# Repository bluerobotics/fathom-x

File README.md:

# Fathom-X and Fathom-E

The Fathom-X and -E Tether Boards are part of Blue Robotics' *Fathom Tether* system. These boards provide interfaces and functionality for the communication methods used with the tether. With the Fathom tether, it is quick and easy to get up and running and interface with your ROV or other application.

The schematic and board layout are designed in EagleCAD.

# Fathom-E (Simple Ethernet) Hardware

## Description

The Fathom-E board provides a simple and economical way to connect the Fathom Tether or a Cat5 cable to an Ethernet jack. It uses all four twisted pairs in the cable and works for tether lengths of up to 100m (per the Ethernet specification).

# Fathom-X Hardware

The Fathom-X board has a few advantages over the Fathom-E interface. It uses a HomePlugAV (IEEE1901) module to send 100 Mbps Ethernet with a single twisted pair. This robust connection works over at least 300m tether lengths. 

Please see the [official documentation](http://docs.bluerobotics.com/fathom-x/) for more information.

## License

The Fathom Ethernet Hardware Design is released under the MIT License.

## Revision History

### Fathom-E 

rev1 - Works but RJ45 misaligned

rev2 - Production version

### Fathom-X

rev1 - Works but poor tether connector used

rev2 - Production version with updated connector

RevB - In progress

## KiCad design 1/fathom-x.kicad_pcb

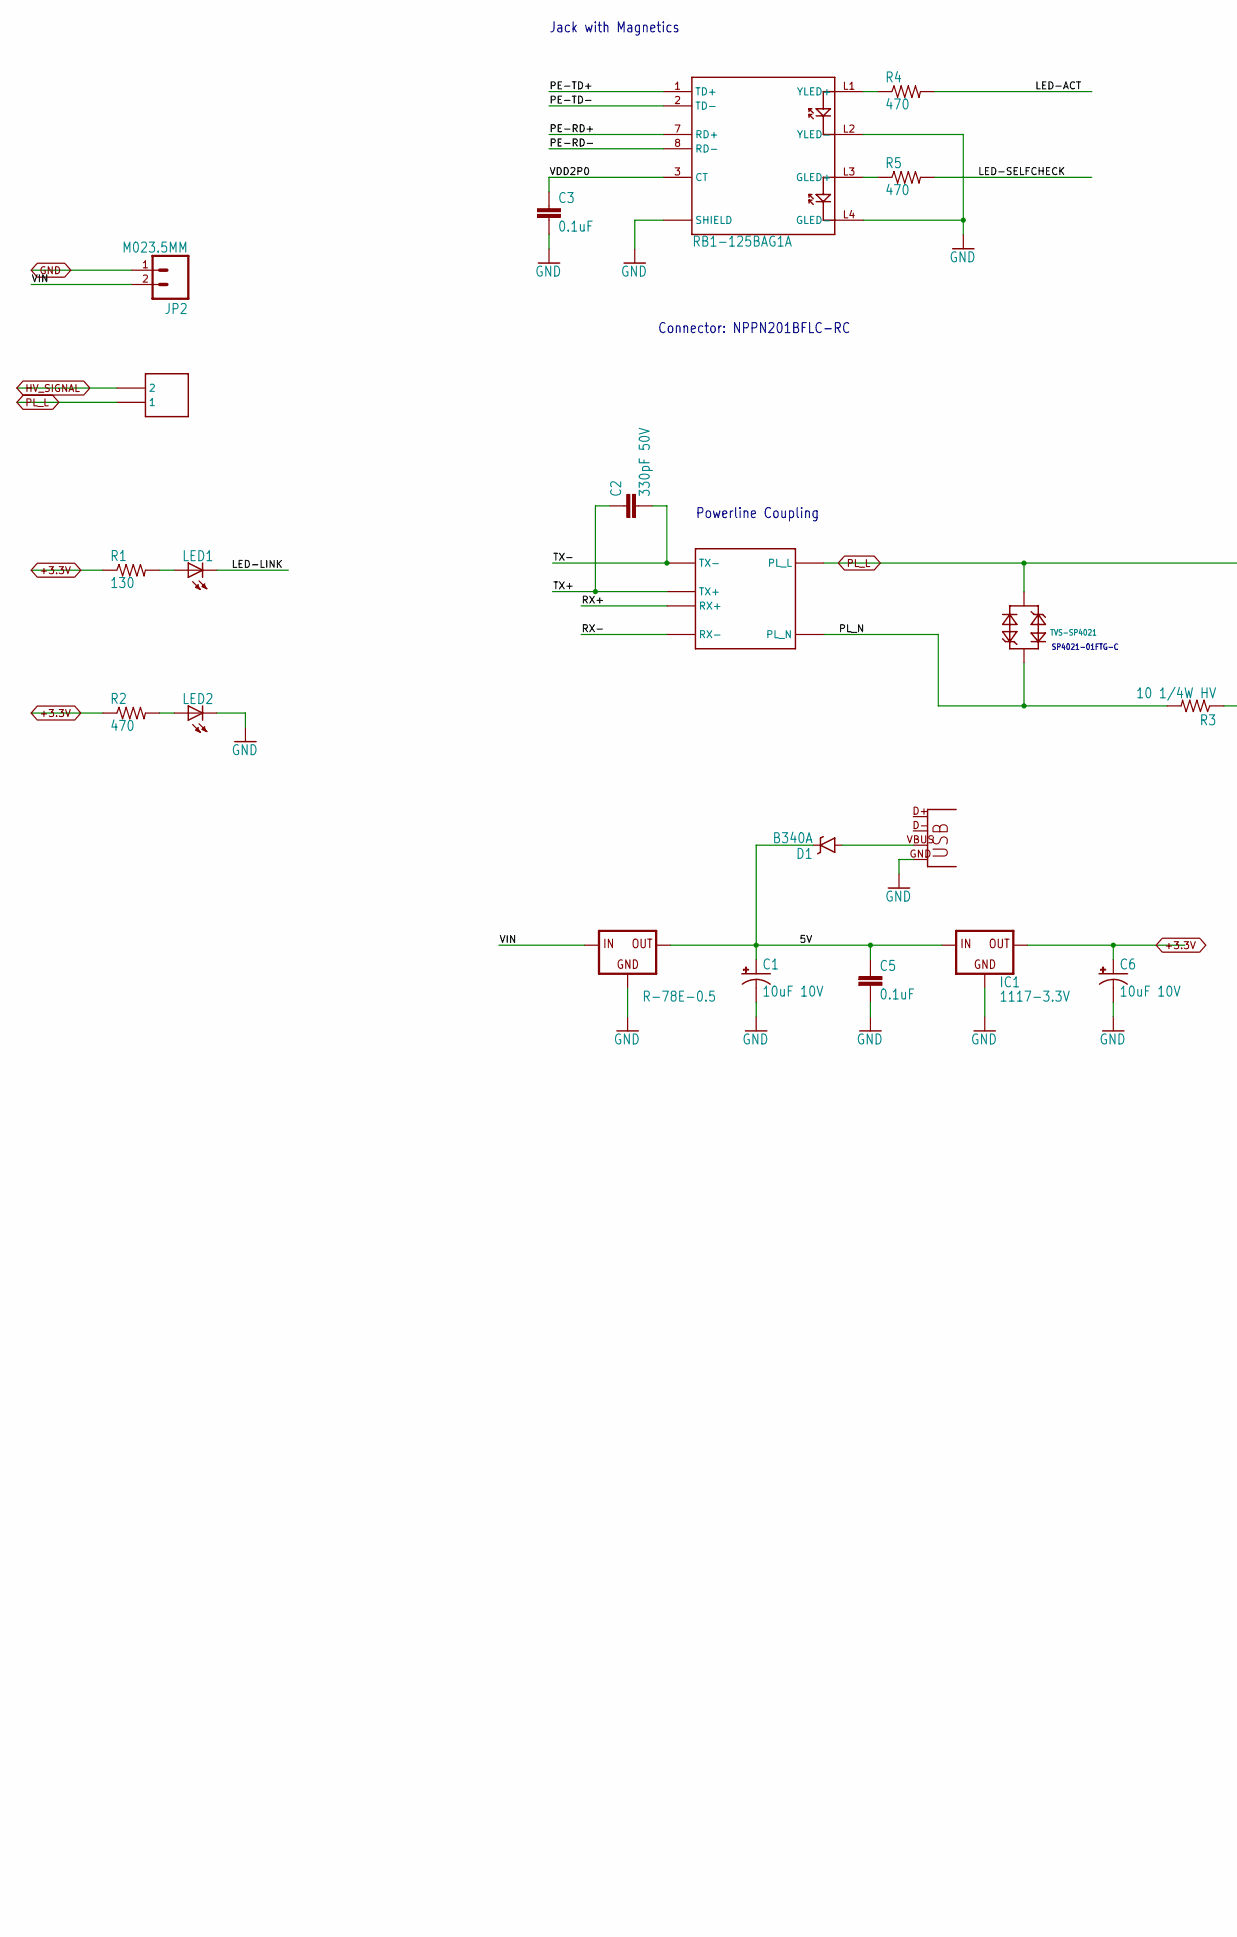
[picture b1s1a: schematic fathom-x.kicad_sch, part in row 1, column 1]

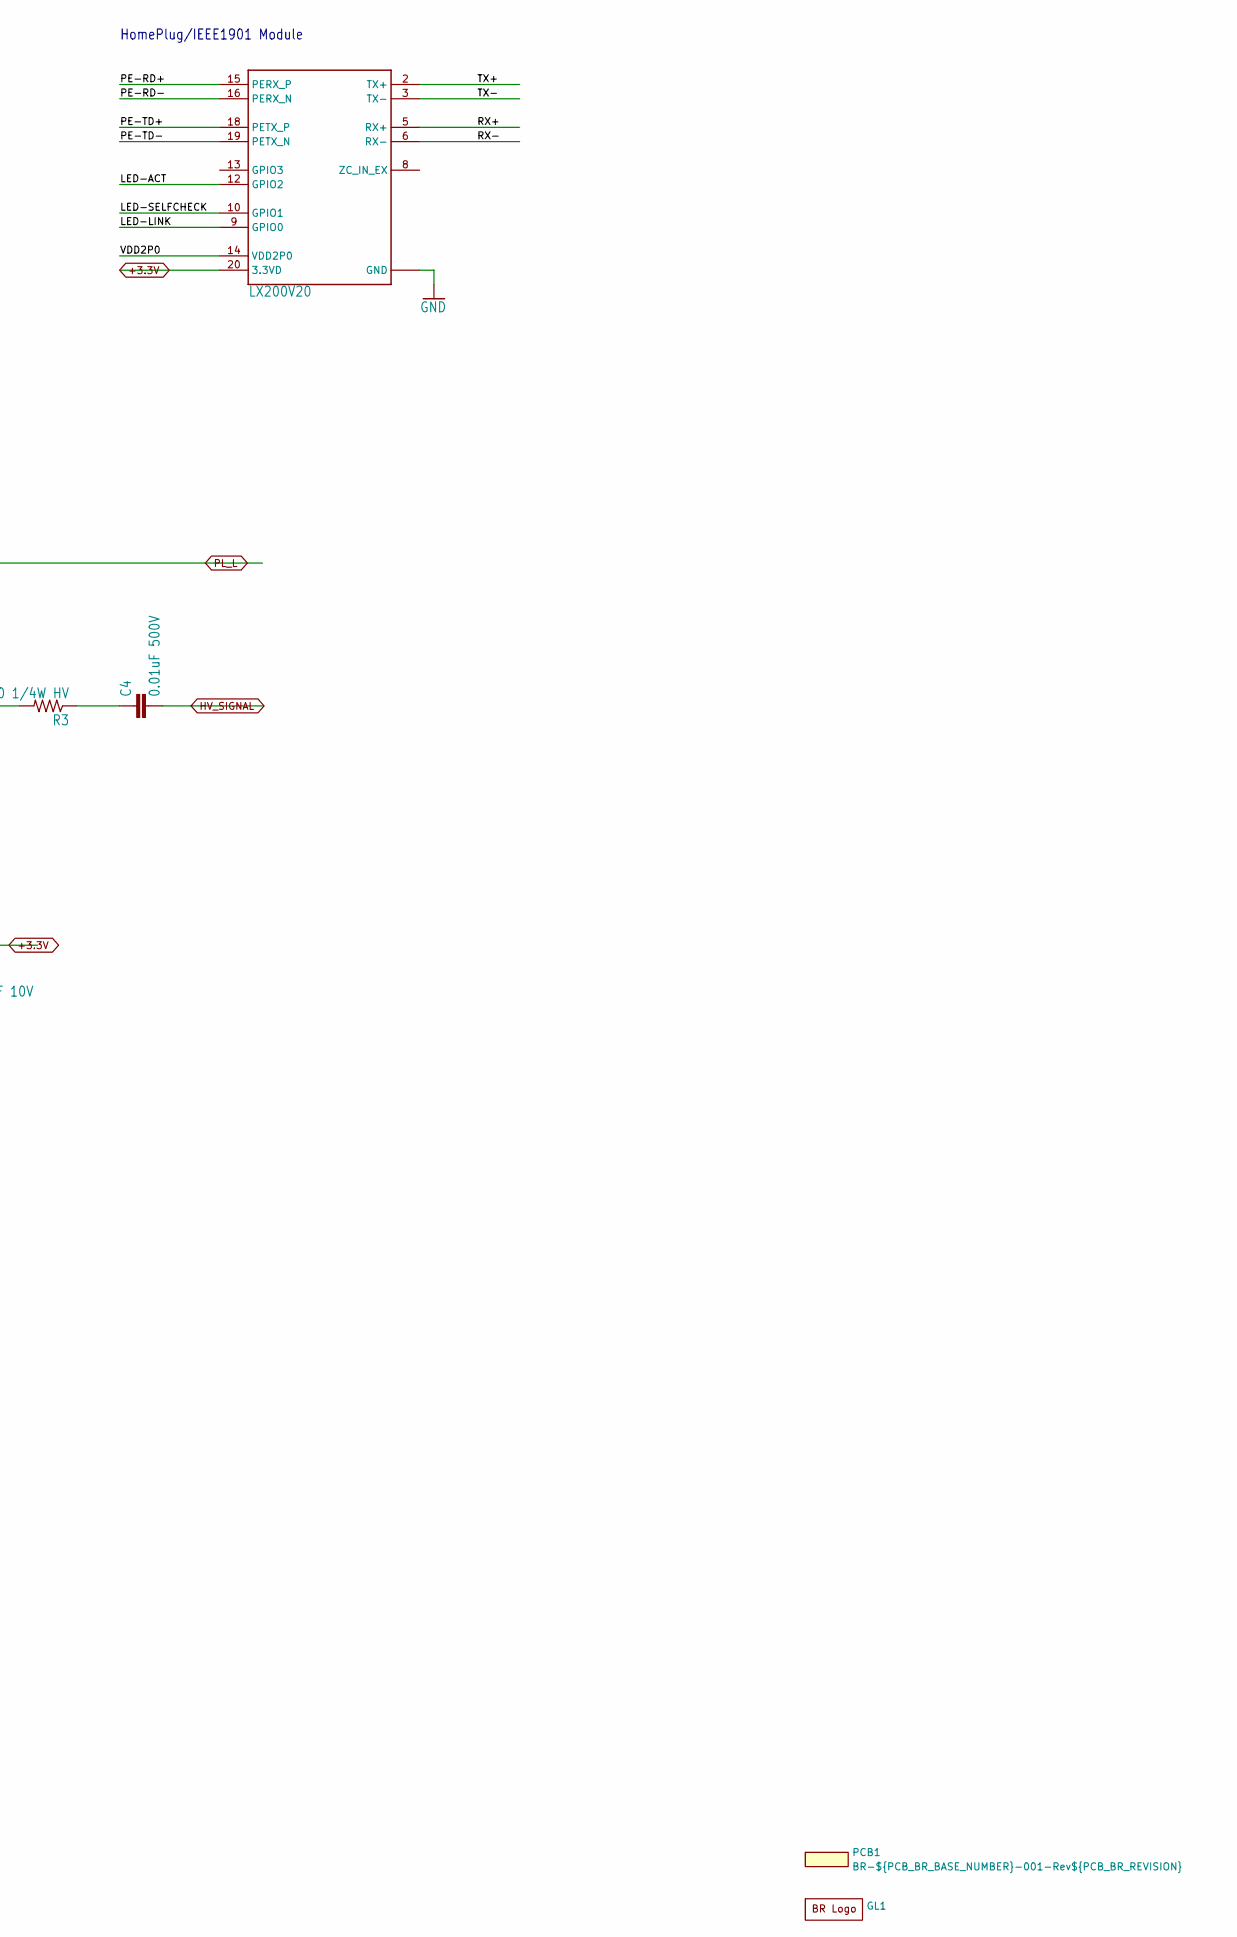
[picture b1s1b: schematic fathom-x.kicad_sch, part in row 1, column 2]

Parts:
C1, C6: 10uF 10V; EIA3216
C2: 330pF 50V; C0805
C3: 0.1uF; C0603
C4: 0.01uF 500V; C1206
C5: 0.1uF; 0603-CAP
D1: B340A; SMA-DIODE
GL1: BR_Logo
IC1: 1117-3.3V; SOT223
JP1: USBSMD; USB-MINIB
JP2: M023.5MM; SCREWTERMINAL-3.5MM-2
LED1, LED2: LEDCHIPLED_0603; CHIPLED_0603
PCB1: Unpopulated PCB; BR_NUMS; Manufacturer Part Num BR-${PCB_BR_BASE_NUMBER}-001-Rev${PCB_B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
R1: 130; R0603
R2, R4, R5: 470; R0603
R3: 10 1/4W HV; R1206
U$1: LX200V20
U$2: UT11403S
U$4: TVS-SP4021; SOD323-BIDIRECTIONAL
U$5: RB1-125BAG1A; RJ45-MAG-WIZNET
U$6: R-78E-0.5
U$8: HEADER-210.16MM; HEADER-10.16MM-2POS

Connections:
+3.3V: C6.A (+), IC1.2 (OUT), R1.1, R2.1, U$1.20 (3.3VD)
/5V: C1.A (+), C5.1, D1.C, IC1.3 (IN), U$6.VOUT (OUT)
/LED-ACT: R4.2, U$1.12 (GPIO2)
/LED-LINK: LED1.C, U$1.9 (GPIO0)
/LED-SELFCHECK: R5.2, U$1.10 (GPIO1)
/PE-RD+: U$1.15 (PERX_P), U$5.7 (RD+)
/PE-RD-: U$1.16 (PERX_N), U$5.8 (RD-)
/PE-TD+: U$1.18 (PETX_P), U$5.1 (TD+)
/PE-TD-: U$1.19 (PETX_N), U$5.2 (TD-)
/PL_N: R3.2, U$2.PL_N, U$4.1
/RX+: U$1.5 (RX+), U$2.RX+
/RX-: U$1.6 (RX-), U$2.RX-
/TX+: C2.1, U$1.2 (TX+), U$2.TX+
/TX-: C2.2, U$1.3 (TX-), U$2.TX-
/VDD2P0: C3.1, U$1.14 (VDD2P0), U$5.3 (CT)
/VIN: JP2.2, U$6.VIN (IN)
GND: C1.C (-), C3.2, C5.2, C6.C (-), IC1.1 (GND), JP1.GND, JP2.1, LED2.C, U$1.1 (GND), U$1.4 (GND), U$1.7 (GND), U$1.11 (GND), U$1.17 (GND), U$5.L2 (YLED-), U$5.L4 (GLED-), U$5.SHIELD0 (SHIELD), U$5.SHIELD1 (SHIELD), U$6.GND
HV_SIGNAL: C4.2, U$8.P$2 (2)
unnamed: C4.1, R3.1
unnamed: D1.A, JP1.VBUS
unnamed: LED1.A, R1.2
unnamed: LED2.A, R2.2
unnamed: R5.1, U$5.L3 (GLED+)
unnamed: R4.1, U$5.L1 (YLED+)
PL_L: U$2.PL_L, U$4.2, U$8.P$1 (1)

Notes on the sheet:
Connector: NPPN201BFLC-RC
Jack with Magnetics
SP4021-01FTG-C
HomePlug/IEEE1901 Module
Powerline Coupling

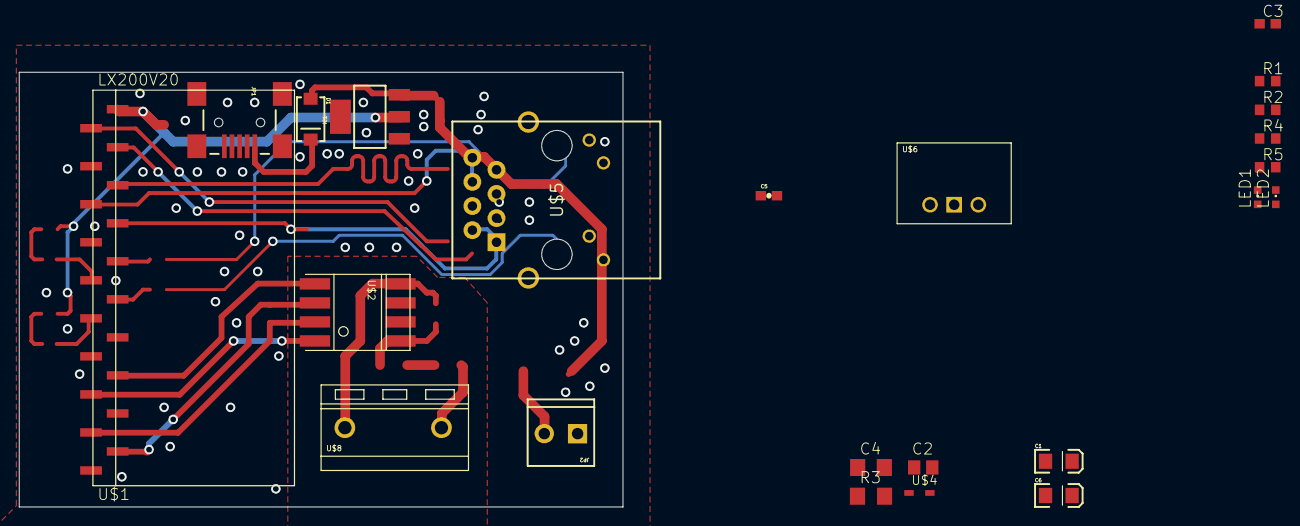
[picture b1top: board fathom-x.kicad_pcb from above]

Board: 2 copper layers, 63.5 x 45.7 mm, 25 parts (0 on the bottom side), 25 nets.

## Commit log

2016-01-27 Base files for Fathom-E.
2016-02-02 First rough layout.
2016-02-03 Updated layout.
2016-02-08 Removed AC components for DC-only support.
2016-02-25 Changing to Ethernet+Power only design.
2016-03-24 Divide to Fathom-E and Fathom-X. Both boards of this revision were ordered.
2016-03-24 Fathom-X: Update signal connector
2016-03-31 Change connector.
2016-04-05 X: Update before order.
2016-05-05 Updated RJ45 position on Fathom-E
2016-06-14 Add Fathom-X schematic.
2016-06-14 Minor Fathom-E change.
2016-06-14 Major update of README.
2016-06-14 Added version notes.
2024-09-19 RevB init
2024-09-19 work
2024-09-19 clean
2024-09-20 did work
2024-09-25 Updated Fathom-X Eagle parts to Kicad
